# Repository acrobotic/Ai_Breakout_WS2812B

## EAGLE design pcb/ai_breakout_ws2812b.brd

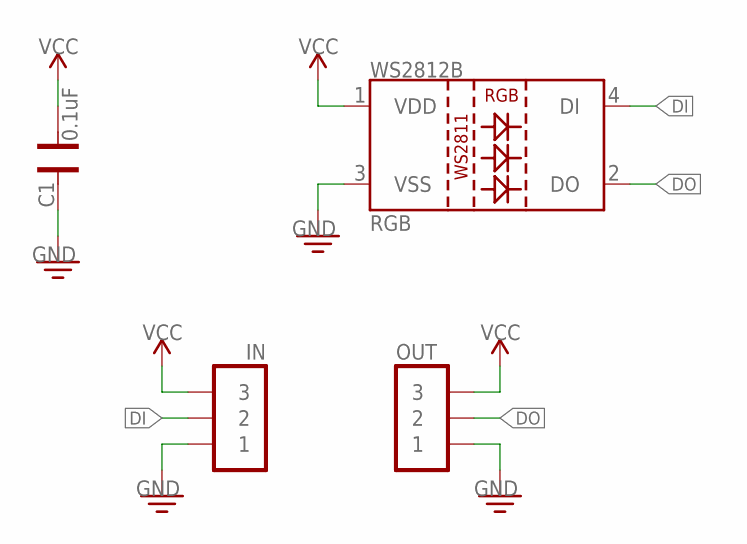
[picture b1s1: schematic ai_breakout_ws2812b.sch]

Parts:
C1: 0.1uF; CAP-0402
IN: 1X03
OUT: 1X03NOFIRST; 1X03-NOFIRST
RGB: LED-WS2812B-SM

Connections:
DI: IN.2, RGB.4 (DI)
DO: OUT.2, RGB.2 (DO)
GND: C1.2, IN.1, OUT.1, RGB.3 (VSS)
VCC: C1.1, IN.3, OUT.3, RGB.1 (VDD)

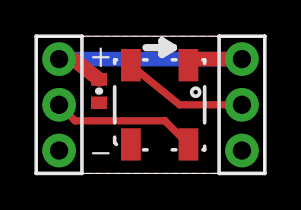
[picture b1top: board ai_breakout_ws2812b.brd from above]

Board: 2 copper layers, 12.7 x 7.6 mm, 5 parts (1 on the bottom side), 4 nets.

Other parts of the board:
U$5: AI-LOGO-XS

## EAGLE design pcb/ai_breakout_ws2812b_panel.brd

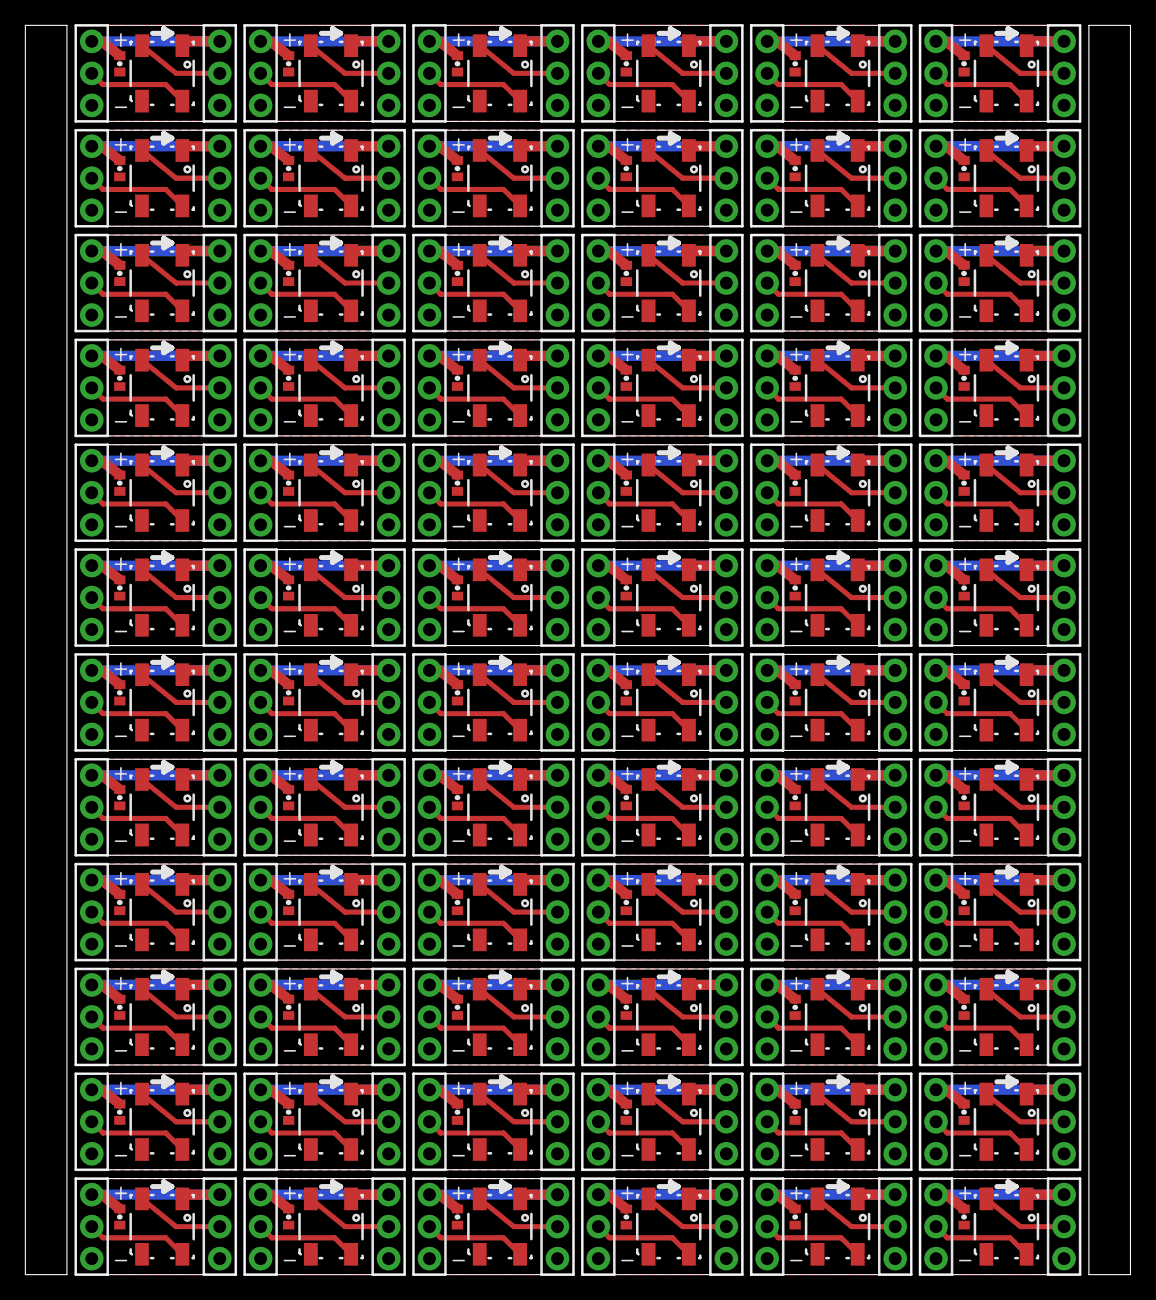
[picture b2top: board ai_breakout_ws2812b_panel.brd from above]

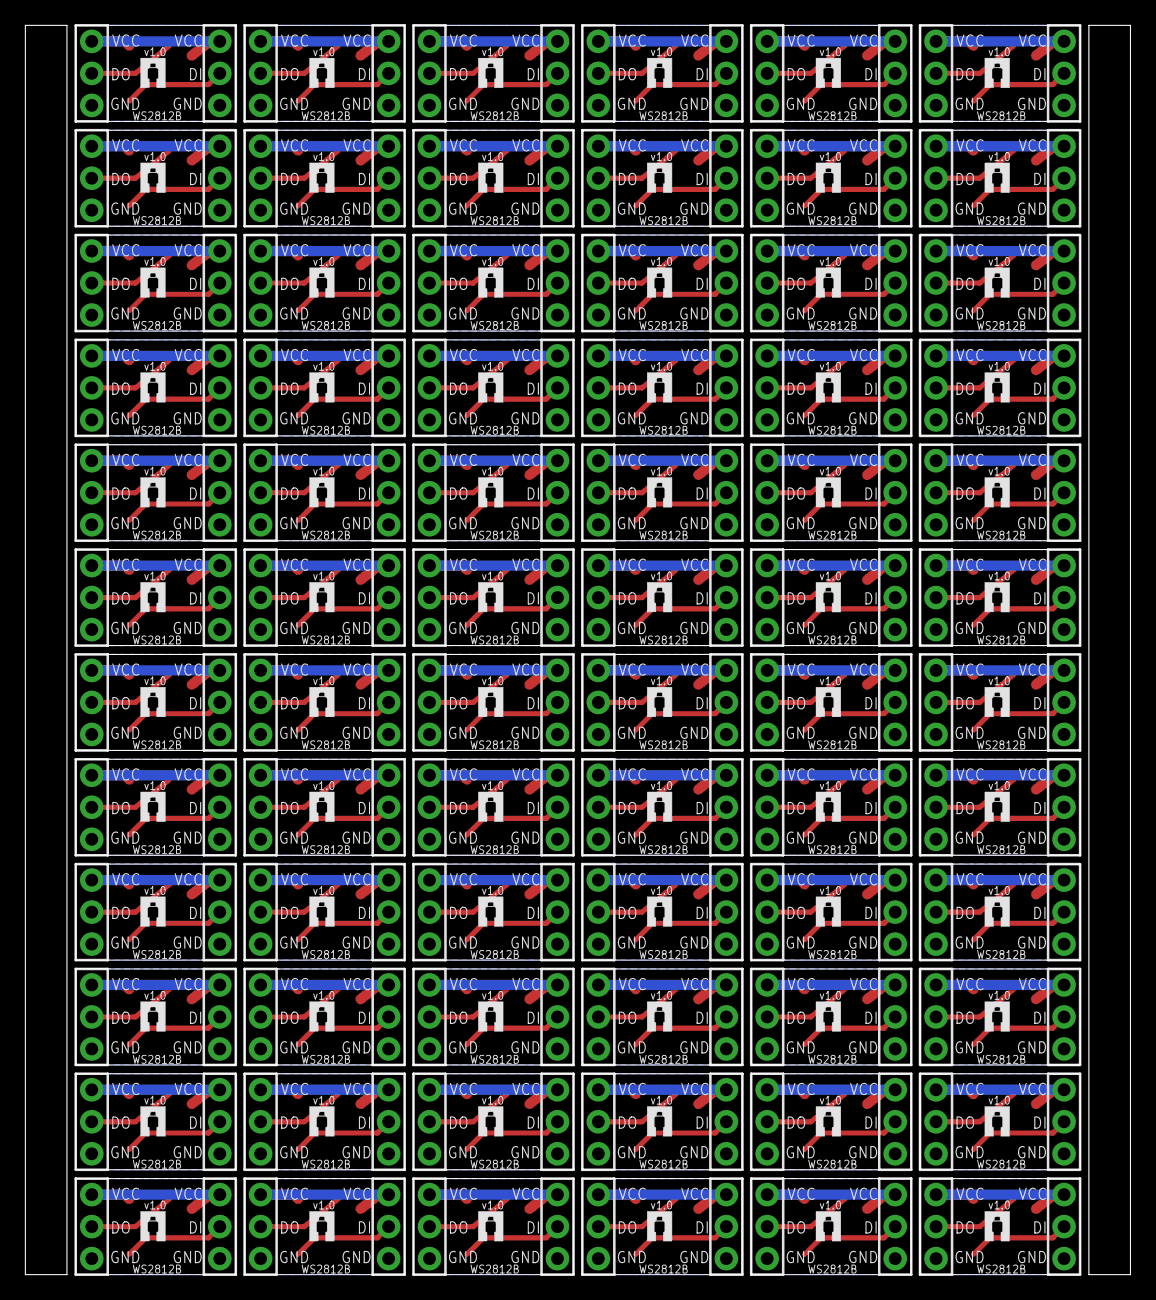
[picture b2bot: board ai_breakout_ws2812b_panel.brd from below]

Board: 2 copper layers, 87.7 x 99.1 mm, 360 parts (72 on the bottom side), 288 nets.

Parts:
C1, C2, C3, C4, C5, C6, C7, C8, C9, C10, C11, C12, C13, C14, C15, C16, C17, C18, C19, C20, C21, C22, C23, C24, C25, C26, C27, C28, C29, C30, C31, C32, C33, C34, C35, C36, C37, C38, C39, C40, C41, C42, C43, C44, C45, C46, C47, C48, C49, C50, C51, C52, C53, C54, C55, C56, C57, C58, C59, C60, C61, C62, C63, C64, C65, C66, C67, C68, C69, C70, C71, C72: 0.1uF; CAP-0402
IN, IN1, IN2, IN3, IN4, IN5, IN6, IN7, IN8, IN9, IN10, IN11, IN12, IN13, IN14, IN15, IN16, IN17, IN18, IN19, IN20, IN21, IN22, IN23, IN24, IN25, IN26, IN27, IN28, IN29, IN30, IN31, IN32, IN33, IN34, IN35, IN36, IN37, IN38, IN39, IN40, IN41, IN42, IN43, IN44, IN45, IN46, IN47, IN48, IN49, IN50, IN51, IN52, IN53, IN54, IN55, IN56, IN57, IN58, IN59, IN60, IN61, IN62, IN63, IN64, IN65, IN66, IN67, IN68, IN69, IN70, IN71: 1X03
OUT, OUT1, OUT2, OUT3, OUT4, OUT5, OUT6, OUT7, OUT8, OUT9, OUT10, OUT11, OUT12, OUT13, OUT14, OUT15, OUT16, OUT17, OUT18, OUT19, OUT20, OUT21, OUT22, OUT23, OUT24, OUT25, OUT26, OUT27, OUT28, OUT29, OUT30, OUT31, OUT32, OUT33, OUT34, OUT35, OUT36, OUT37, OUT38, OUT39, OUT40, OUT41, OUT42, OUT43, OUT44, OUT45, OUT46, OUT47, OUT48, OUT49, OUT50, OUT51, OUT52, OUT53, OUT54, OUT55, OUT56, OUT57, OUT58, OUT59, OUT60, OUT61, OUT62, OUT63, OUT64, OUT65, OUT66, OUT67, OUT68, OUT69, OUT70, OUT71: 1X03NOFIRST; 1X03-NOFIRST
RGB, RGB1, RGB2, RGB3, RGB4, RGB5, RGB6, RGB7, RGB8, RGB9, RGB10, RGB11, RGB12, RGB13, RGB14, RGB15, RGB16, RGB17, RGB18, RGB19, RGB20, RGB21, RGB22, RGB23, RGB24, RGB25, RGB26, RGB27, RGB28, RGB29, RGB30, RGB31, RGB32, RGB33, RGB34, RGB35, RGB36, RGB37, RGB38, RGB39, RGB40, RGB41, RGB42, RGB43, RGB44, RGB45, RGB46, RGB47, RGB48, RGB49, RGB50, RGB51, RGB52, RGB53, RGB54, RGB55, RGB56, RGB57, RGB58, RGB59, RGB60, RGB61, RGB62, RGB63, RGB64, RGB65, RGB66, RGB67, RGB68, RGB69, RGB70, RGB71: LED-WS2812B-SM
U$1, U$2, U$3, U$4, U$5, U$6, U$7, U$8, U$9, U$10, U$11, U$12, U$13, U$14, U$15, U$16, U$17, U$18, U$19, U$20, U$21, U$22, U$23, U$24, U$25, U$26, U$27, U$28, U$29, U$30, U$31, U$32, U$33, U$34, U$35, U$36, U$37, U$38, U$39, U$40, U$41, U$42, U$43, U$44, U$45, U$46, U$47, U$48, U$49, U$50, U$51, U$52, U$53, U$54, U$55, U$56, U$57, U$58, U$59, U$60, U$61, U$62, U$63, U$64, U$65, U$66, U$67, U$68, U$69, U$70, U$71, U$72: AI-LOGO-XS

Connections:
DI: IN.2, RGB.4
DI1: IN1.2, RGB1.4
DI2: IN2.2, RGB2.4
DI3: IN3.2, RGB3.4
DI4: IN4.2, RGB4.4
DI5: IN5.2, RGB5.4
DI6: IN6.2, RGB6.4
DI7: IN7.2, RGB7.4
DI8: IN8.2, RGB8.4
DI9: IN9.2, RGB9.4
DI10: IN10.2, RGB10.4
DI11: IN11.2, RGB11.4
DI12: IN12.2, RGB12.4
DI13: IN13.2, RGB13.4
DI14: IN14.2, RGB14.4
DI15: IN15.2, RGB15.4
DI16: IN16.2, RGB16.4
DI17: IN17.2, RGB17.4
DI18: IN18.2, RGB18.4
DI19: IN19.2, RGB19.4
DI20: IN20.2, RGB20.4
DI21: IN21.2, RGB21.4
DI22: IN22.2, RGB22.4
DI23: IN23.2, RGB23.4
DI24: IN24.2, RGB24.4
DI25: IN25.2, RGB25.4
DI26: IN26.2, RGB26.4
DI27: IN27.2, RGB27.4
DI28: IN28.2, RGB28.4
DI29: IN29.2, RGB29.4
DI30: IN30.2, RGB30.4
DI31: IN31.2, RGB31.4
DI32: IN32.2, RGB32.4
DI33: IN33.2, RGB33.4
DI34: IN34.2, RGB34.4
DI35: IN35.2, RGB35.4
DI36: IN36.2, RGB36.4
DI37: IN37.2, RGB37.4
DI38: IN38.2, RGB38.4
DI39: IN39.2, RGB39.4
DI40: IN40.2, RGB40.4
DI41: IN41.2, RGB41.4
DI42: IN42.2, RGB42.4
DI43: IN43.2, RGB43.4
DI44: IN44.2, RGB44.4
DI45: IN45.2, RGB45.4
DI46: IN46.2, RGB46.4
DI47: IN47.2, RGB47.4
DI48: IN48.2, RGB48.4
DI49: IN49.2, RGB49.4
DI50: IN50.2, RGB50.4
DI51: IN51.2, RGB51.4
DI52: IN52.2, RGB52.4
DI53: IN53.2, RGB53.4
DI54: IN54.2, RGB54.4
DI55: IN55.2, RGB55.4
DI56: IN56.2, RGB56.4
DI57: IN57.2, RGB57.4
DI58: IN58.2, RGB58.4
DI59: IN59.2, RGB59.4
DI60: IN60.2, RGB60.4
DI61: IN61.2, RGB61.4
DI62: IN62.2, RGB62.4
DI63: IN63.2, RGB63.4
DI64: IN64.2, RGB64.4
DI65: IN65.2, RGB65.4
DI66: IN66.2, RGB66.4
DI67: IN67.2, RGB67.4
DI68: IN68.2, RGB68.4
DI69: IN69.2, RGB69.4
DI70: IN70.2, RGB70.4
DI71: IN71.2, RGB71.4
DO: OUT.2, RGB.2
DO1: OUT1.2, RGB1.2
DO2: OUT2.2, RGB2.2
DO3: OUT3.2, RGB3.2
DO4: OUT4.2, RGB4.2
DO5: OUT5.2, RGB5.2
DO6: OUT6.2, RGB6.2
DO7: OUT7.2, RGB7.2
DO8: OUT8.2, RGB8.2
DO9: OUT9.2, RGB9.2
DO10: OUT10.2, RGB10.2
DO11: OUT11.2, RGB11.2
DO12: OUT12.2, RGB12.2
DO13: OUT13.2, RGB13.2
DO14: OUT14.2, RGB14.2
DO15: OUT15.2, RGB15.2
DO16: OUT16.2, RGB16.2
DO17: OUT17.2, RGB17.2
DO18: OUT18.2, RGB18.2
DO19: OUT19.2, RGB19.2
DO20: OUT20.2, RGB20.2
DO21: OUT21.2, RGB21.2
DO22: OUT22.2, RGB22.2
DO23: OUT23.2, RGB23.2
DO24: OUT24.2, RGB24.2
DO25: OUT25.2, RGB25.2
DO26: OUT26.2, RGB26.2
DO27: OUT27.2, RGB27.2
DO28: OUT28.2, RGB28.2
DO29: OUT29.2, RGB29.2
DO30: OUT30.2, RGB30.2
DO31: OUT31.2, RGB31.2
DO32: OUT32.2, RGB32.2
DO33: OUT33.2, RGB33.2
DO34: OUT34.2, RGB34.2
DO35: OUT35.2, RGB35.2
DO36: OUT36.2, RGB36.2
DO37: OUT37.2, RGB37.2
DO38: OUT38.2, RGB38.2
DO39: OUT39.2, RGB39.2
DO40: OUT40.2, RGB40.2
DO41: OUT41.2, RGB41.2
DO42: OUT42.2, RGB42.2
DO43: OUT43.2, RGB43.2
DO44: OUT44.2, RGB44.2
DO45: OUT45.2, RGB45.2
DO46: OUT46.2, RGB46.2
DO47: OUT47.2, RGB47.2
DO48: OUT48.2, RGB48.2
DO49: OUT49.2, RGB49.2
DO50: OUT50.2, RGB50.2
DO51: OUT51.2, RGB51.2
DO52: OUT52.2, RGB52.2
DO53: OUT53.2, RGB53.2
DO54: OUT54.2, RGB54.2
DO55: OUT55.2, RGB55.2
DO56: OUT56.2, RGB56.2
DO57: OUT57.2, RGB57.2
DO58: OUT58.2, RGB58.2
DO59: OUT59.2, RGB59.2
DO60: OUT60.2, RGB60.2
DO61: OUT61.2, RGB61.2
DO62: OUT62.2, RGB62.2
DO63: OUT63.2, RGB63.2
DO64: OUT64.2, RGB64.2
DO65: OUT65.2, RGB65.2
DO66: OUT66.2, RGB66.2
DO67: OUT67.2, RGB67.2
DO68: OUT68.2, RGB68.2
DO69: OUT69.2, RGB69.2
DO70: OUT70.2, RGB70.2
DO71: OUT71.2, RGB71.2
GND: C1.2, IN.1, OUT.1, RGB.3
GND1: C2.2, IN1.1, OUT1.1, RGB1.3
GND2: C3.2, IN2.1, OUT2.1, RGB2.3
GND3: C4.2, IN3.1, OUT3.1, RGB3.3
GND4: C5.2, IN4.1, OUT4.1, RGB4.3
GND5: C6.2, IN5.1, OUT5.1, RGB5.3
GND6: C7.2, IN6.1, OUT6.1, RGB6.3
GND7: C8.2, IN7.1, OUT7.1, RGB7.3
GND8: C9.2, IN8.1, OUT8.1, RGB8.3
GND9: C10.2, IN9.1, OUT9.1, RGB9.3
GND10: C11.2, IN10.1, OUT10.1, RGB10.3
GND11: C12.2, IN11.1, OUT11.1, RGB11.3
GND12: C13.2, IN12.1, OUT12.1, RGB12.3
GND13: C14.2, IN13.1, OUT13.1, RGB13.3
GND14: C15.2, IN14.1, OUT14.1, RGB14.3
GND15: C16.2, IN15.1, OUT15.1, RGB15.3
GND16: C17.2, IN16.1, OUT16.1, RGB16.3
GND17: C18.2, IN17.1, OUT17.1, RGB17.3
GND18: C19.2, IN18.1, OUT18.1, RGB18.3
GND19: C20.2, IN19.1, OUT19.1, RGB19.3
GND20: C21.2, IN20.1, OUT20.1, RGB20.3
GND21: C22.2, IN21.1, OUT21.1, RGB21.3
GND22: C23.2, IN22.1, OUT22.1, RGB22.3
GND23: C24.2, IN23.1, OUT23.1, RGB23.3
GND24: C25.2, IN24.1, OUT24.1, RGB24.3
GND25: C26.2, IN25.1, OUT25.1, RGB25.3
GND26: C27.2, IN26.1, OUT26.1, RGB26.3
GND27: C28.2, IN27.1, OUT27.1, RGB27.3
GND28: C29.2, IN28.1, OUT28.1, RGB28.3
GND29: C30.2, IN29.1, OUT29.1, RGB29.3
GND30: C31.2, IN30.1, OUT30.1, RGB30.3
GND31: C32.2, IN31.1, OUT31.1, RGB31.3
GND32: C33.2, IN32.1, OUT32.1, RGB32.3
GND33: C34.2, IN33.1, OUT33.1, RGB33.3
GND34: C35.2, IN34.1, OUT34.1, RGB34.3
GND35: C36.2, IN35.1, OUT35.1, RGB35.3
GND36: C37.2, IN36.1, OUT36.1, RGB36.3
GND37: C38.2, IN37.1, OUT37.1, RGB37.3
GND38: C39.2, IN38.1, OUT38.1, RGB38.3
GND39: C40.2, IN39.1, OUT39.1, RGB39.3
GND40: C41.2, IN40.1, OUT40.1, RGB40.3
GND41: C42.2, IN41.1, OUT41.1, RGB41.3
GND42: C43.2, IN42.1, OUT42.1, RGB42.3
GND43: C44.2, IN43.1, OUT43.1, RGB43.3
GND44: C45.2, IN44.1, OUT44.1, RGB44.3
GND45: C46.2, IN45.1, OUT45.1, RGB45.3
GND46: C47.2, IN46.1, OUT46.1, RGB46.3
GND47: C48.2, IN47.1, OUT47.1, RGB47.3
GND48: C49.2, IN48.1, OUT48.1, RGB48.3
GND49: C50.2, IN49.1, OUT49.1, RGB49.3
GND50: C51.2, IN50.1, OUT50.1, RGB50.3
GND51: C52.2, IN51.1, OUT51.1, RGB51.3
GND52: C53.2, IN52.1, OUT52.1, RGB52.3
GND53: C54.2, IN53.1, OUT53.1, RGB53.3
GND54: C55.2, IN54.1, OUT54.1, RGB54.3
GND55: C56.2, IN55.1, OUT55.1, RGB55.3
GND56: C57.2, IN56.1, OUT56.1, RGB56.3
GND57: C58.2, IN57.1, OUT57.1, RGB57.3
GND58: C59.2, IN58.1, OUT58.1, RGB58.3
GND59: C60.2, IN59.1, OUT59.1, RGB59.3
GND60: C61.2, IN60.1, OUT60.1, RGB60.3
GND61: C62.2, IN61.1, OUT61.1, RGB61.3
GND62: C63.2, IN62.1, OUT62.1, RGB62.3
GND63: C64.2, IN63.1, OUT63.1, RGB63.3
GND64: C65.2, IN64.1, OUT64.1, RGB64.3
GND65: C66.2, IN65.1, OUT65.1, RGB65.3
GND66: C67.2, IN66.1, OUT66.1, RGB66.3
GND67: C68.2, IN67.1, OUT67.1, RGB67.3
GND68: C69.2, IN68.1, OUT68.1, RGB68.3
GND69: C70.2, IN69.1, OUT69.1, RGB69.3
GND70: C71.2, IN70.1, OUT70.1, RGB70.3
GND71: C72.2, IN71.1, OUT71.1, RGB71.3
VCC: C1.1, IN.3, OUT.3, RGB.1
VCC1: C2.1, IN1.3, OUT1.3, RGB1.1
VCC2: C3.1, IN2.3, OUT2.3, RGB2.1
VCC3: C4.1, IN3.3, OUT3.3, RGB3.1
VCC4: C5.1, IN4.3, OUT4.3, RGB4.1
VCC5: C6.1, IN5.3, OUT5.3, RGB5.1
VCC6: C7.1, IN6.3, OUT6.3, RGB6.1
VCC7: C8.1, IN7.3, OUT7.3, RGB7.1
VCC8: C9.1, IN8.3, OUT8.3, RGB8.1
VCC9: C10.1, IN9.3, OUT9.3, RGB9.1
VCC10: C11.1, IN10.3, OUT10.3, RGB10.1
VCC11: C12.1, IN11.3, OUT11.3, RGB11.1
VCC12: C13.1, IN12.3, OUT12.3, RGB12.1
VCC13: C14.1, IN13.3, OUT13.3, RGB13.1
VCC14: C15.1, IN14.3, OUT14.3, RGB14.1
VCC15: C16.1, IN15.3, OUT15.3, RGB15.1
VCC16: C17.1, IN16.3, OUT16.3, RGB16.1
VCC17: C18.1, IN17.3, OUT17.3, RGB17.1
VCC18: C19.1, IN18.3, OUT18.3, RGB18.1
VCC19: C20.1, IN19.3, OUT19.3, RGB19.1
VCC20: C21.1, IN20.3, OUT20.3, RGB20.1
VCC21: C22.1, IN21.3, OUT21.3, RGB21.1
VCC22: C23.1, IN22.3, OUT22.3, RGB22.1
VCC23: C24.1, IN23.3, OUT23.3, RGB23.1
VCC24: C25.1, IN24.3, OUT24.3, RGB24.1
VCC25: C26.1, IN25.3, OUT25.3, RGB25.1
VCC26: C27.1, IN26.3, OUT26.3, RGB26.1
VCC27: C28.1, IN27.3, OUT27.3, RGB27.1
VCC28: C29.1, IN28.3, OUT28.3, RGB28.1
VCC29: C30.1, IN29.3, OUT29.3, RGB29.1
VCC30: C31.1, IN30.3, OUT30.3, RGB30.1
VCC31: C32.1, IN31.3, OUT31.3, RGB31.1
VCC32: C33.1, IN32.3, OUT32.3, RGB32.1
VCC33: C34.1, IN33.3, OUT33.3, RGB33.1
VCC34: C35.1, IN34.3, OUT34.3, RGB34.1
VCC35: C36.1, IN35.3, OUT35.3, RGB35.1
VCC36: C37.1, IN36.3, OUT36.3, RGB36.1
VCC37: C38.1, IN37.3, OUT37.3, RGB37.1
VCC38: C39.1, IN38.3, OUT38.3, RGB38.1
VCC39: C40.1, IN39.3, OUT39.3, RGB39.1
VCC40: C41.1, IN40.3, OUT40.3, RGB40.1
VCC41: C42.1, IN41.3, OUT41.3, RGB41.1
VCC42: C43.1, IN42.3, OUT42.3, RGB42.1
VCC43: C44.1, IN43.3, OUT43.3, RGB43.1
VCC44: C45.1, IN44.3, OUT44.3, RGB44.1
VCC45: C46.1, IN45.3, OUT45.3, RGB45.1
VCC46: C47.1, IN46.3, OUT46.3, RGB46.1
VCC47: C48.1, IN47.3, OUT47.3, RGB47.1
VCC48: C49.1, IN48.3, OUT48.3, RGB48.1
VCC49: C50.1, IN49.3, OUT49.3, RGB49.1
VCC50: C51.1, IN50.3, OUT50.3, RGB50.1
VCC51: C52.1, IN51.3, OUT51.3, RGB51.1
VCC52: C53.1, IN52.3, OUT52.3, RGB52.1
VCC53: C54.1, IN53.3, OUT53.3, RGB53.1
VCC54: C55.1, IN54.3, OUT54.3, RGB54.1
VCC55: C56.1, IN55.3, OUT55.3, RGB55.1
VCC56: C57.1, IN56.3, OUT56.3, RGB56.1
VCC57: C58.1, IN57.3, OUT57.3, RGB57.1
VCC58: C59.1, IN58.3, OUT58.3, RGB58.1
VCC59: C60.1, IN59.3, OUT59.3, RGB59.1
VCC60: C61.1, IN60.3, OUT60.3, RGB60.1
VCC61: C62.1, IN61.3, OUT61.3, RGB61.1
VCC62: C63.1, IN62.3, OUT62.3, RGB62.1
VCC63: C64.1, IN63.3, OUT63.3, RGB63.1
VCC64: C65.1, IN64.3, OUT64.3, RGB64.1
VCC65: C66.1, IN65.3, OUT65.3, RGB65.1
VCC66: C67.1, IN66.3, OUT66.3, RGB66.1
VCC67: C68.1, IN67.3, OUT67.3, RGB67.1
VCC68: C69.1, IN68.3, OUT68.3, RGB68.1
VCC69: C70.1, IN69.3, OUT69.3, RGB69.1
VCC70: C71.1, IN70.3, OUT70.3, RGB70.1
VCC71: C72.1, IN71.3, OUT71.3, RGB71.1

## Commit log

2015-02-26 First commit.
2015-02-26 adding panelized version
